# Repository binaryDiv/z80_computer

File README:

This is a repository for my personal Z80 computer project.

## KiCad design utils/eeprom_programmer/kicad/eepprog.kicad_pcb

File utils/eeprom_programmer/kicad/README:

Note: The Kicad files seem to be broken. :(

The actual hardware is built on a perfboard right now and slightly different to the Kicad scheme (?).

TODO: Fix Kicad files to actually produce a PCB sometime. :3

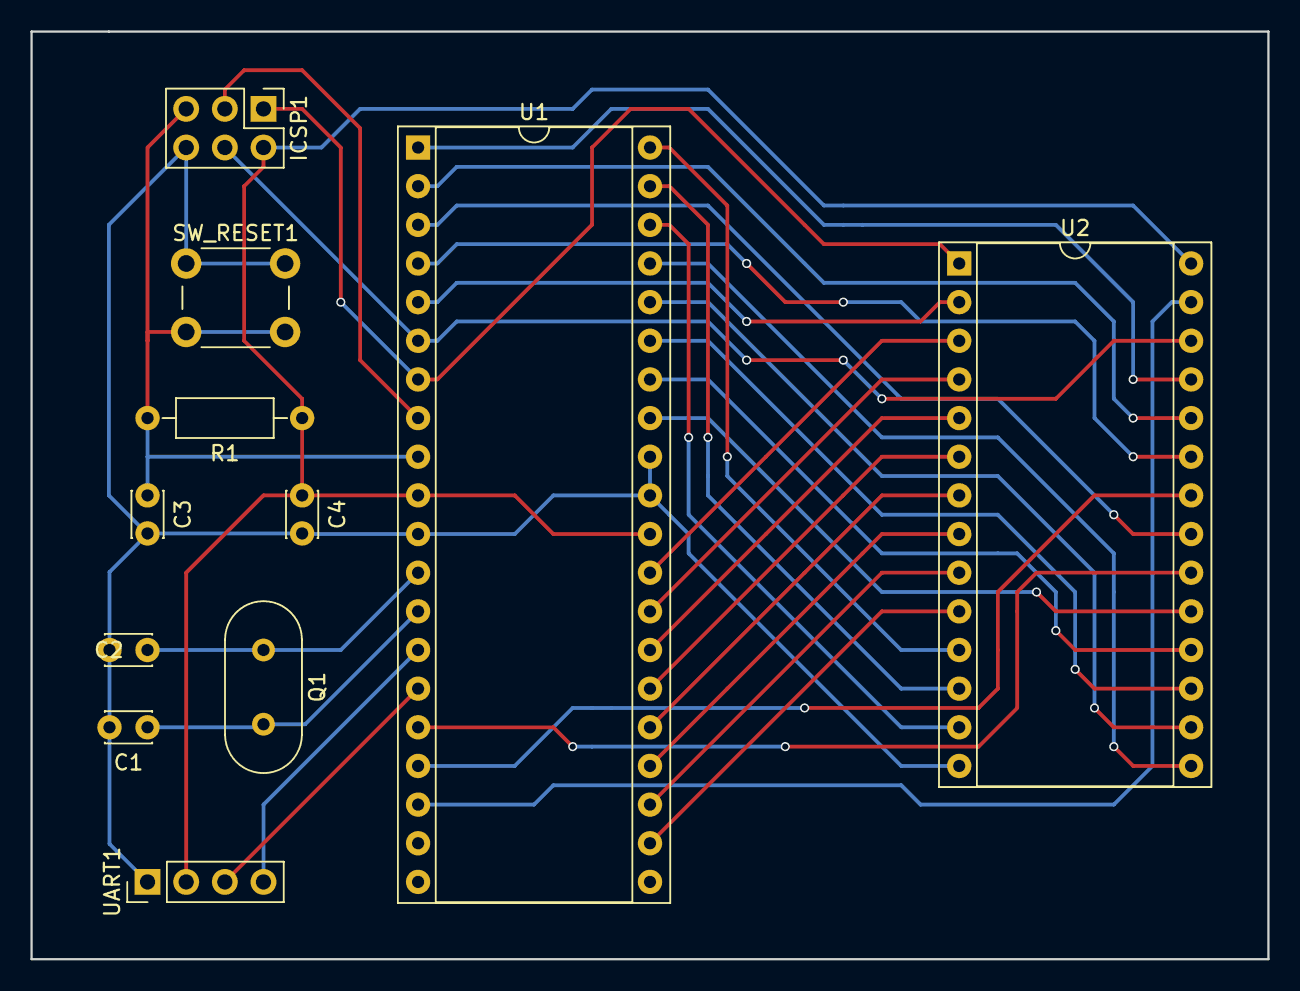
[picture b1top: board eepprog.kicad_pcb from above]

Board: 2 copper layers, 81.3 x 61.0 mm, 11 parts (0 on the bottom side), 34 nets.

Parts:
C1, C2: 22pF; C_Disc_D3.0mm_W2.0mm_P2.50mm
C3: 47nF; C_Disc_D3.0mm_W2.0mm_P2.50mm
C4: 100nF; C_Disc_D3.0mm_W2.0mm_P2.50mm
ICSP1: Conn_02x03_Odd_Even; Pin_Header_Straight_2x03_Pitch2.54mm
Q1: 16MHz; Crystal_HC49-U_Vertical
R1: 10k; R_Axial_DIN0207_L6.3mm_D2.5mm_P10.16mm_Horizontal
SW_RESET1: SW_Push; SW_PUSH_6mm_h4.3mm
U1: ATMEGA16-16PU; DIP-40_W15.24mm_Socket
U2: 28C256; DIP-28_W15.24mm_Socket
UART1: Conn_01x04; Pin_Header_Straight_1x04_Pitch2.54mm

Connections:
GND: C1.2, C2.2, C3.2, C4.2, ICSP1.6, SW_RESET1.1, U1.11, U1.31, U1.32, U2.14, UART1.1
unnamed: C1.1, Q1.2, U1.13
unnamed: C2.1, Q1.1, U1.12
unnamed: C3.1, ICSP1.5, R1.2, SW_RESET1.2, U1.9
unnamed: ICSP1.1, U1.7, U2.1
unnamed: ICSP1.3, U1.8
unnamed: ICSP1.4, U1.6, U2.26
unnamed: U1.1, U2.25
unnamed: U1.2, U2.24
unnamed: U1.3, U2.21
unnamed: U1.4, U2.23
unnamed: U1.5, U2.2
unnamed: U1.14, UART1.4
unnamed: U1.15, UART1.3
unnamed: U1.16, U2.20
unnamed: U1.17, U2.22
unnamed: U1.18, U2.27
unnamed: U1.22, U2.10
unnamed: U1.23, U2.9
unnamed: U1.24, U2.8
unnamed: U1.25, U2.7
unnamed: U1.26, U2.6
unnamed: U1.27, U2.5
unnamed: U1.28, U2.4
unnamed: U1.29, U2.3
unnamed: U1.33, U2.19
unnamed: U1.34, U2.18
unnamed: U1.35, U2.17
unnamed: U1.36, U2.16
unnamed: U1.37, U2.15
unnamed: U1.38, U2.13
unnamed: U1.39, U2.12
unnamed: U1.40, U2.11
VCC: C4.1, ICSP1.2, R1.1, U1.10, U1.30, U2.28, UART1.2

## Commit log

2018-08-08 EEPROM programmer initial commit.
2018-08-08 Added Kicad files.
    TODO: check if they still work...)
2018-08-08 Added (unfinished) firmware code.
2018-08-08 EEPROM programming tool (python): Initial commit.
2018-08-08 Added .gitignore.
2018-08-24 Added ".*.swp" to .gitignore
2018-08-24 Argument parsing, added usage()
2018-08-24 Added text file describing USB-serial adapter pins
2018-08-24 Serial setup, test command
2018-08-24 Better handling of \r and \n in uartGetLine()
2018-08-25 Basic protocol handling, command parsing
2018-08-25 Implemented TESTREAD/TESTWRITE
2018-08-25 Send TESTREAD and receive data
2018-08-28 Small fix
2018-08-28 Added tokenizeCommand function
